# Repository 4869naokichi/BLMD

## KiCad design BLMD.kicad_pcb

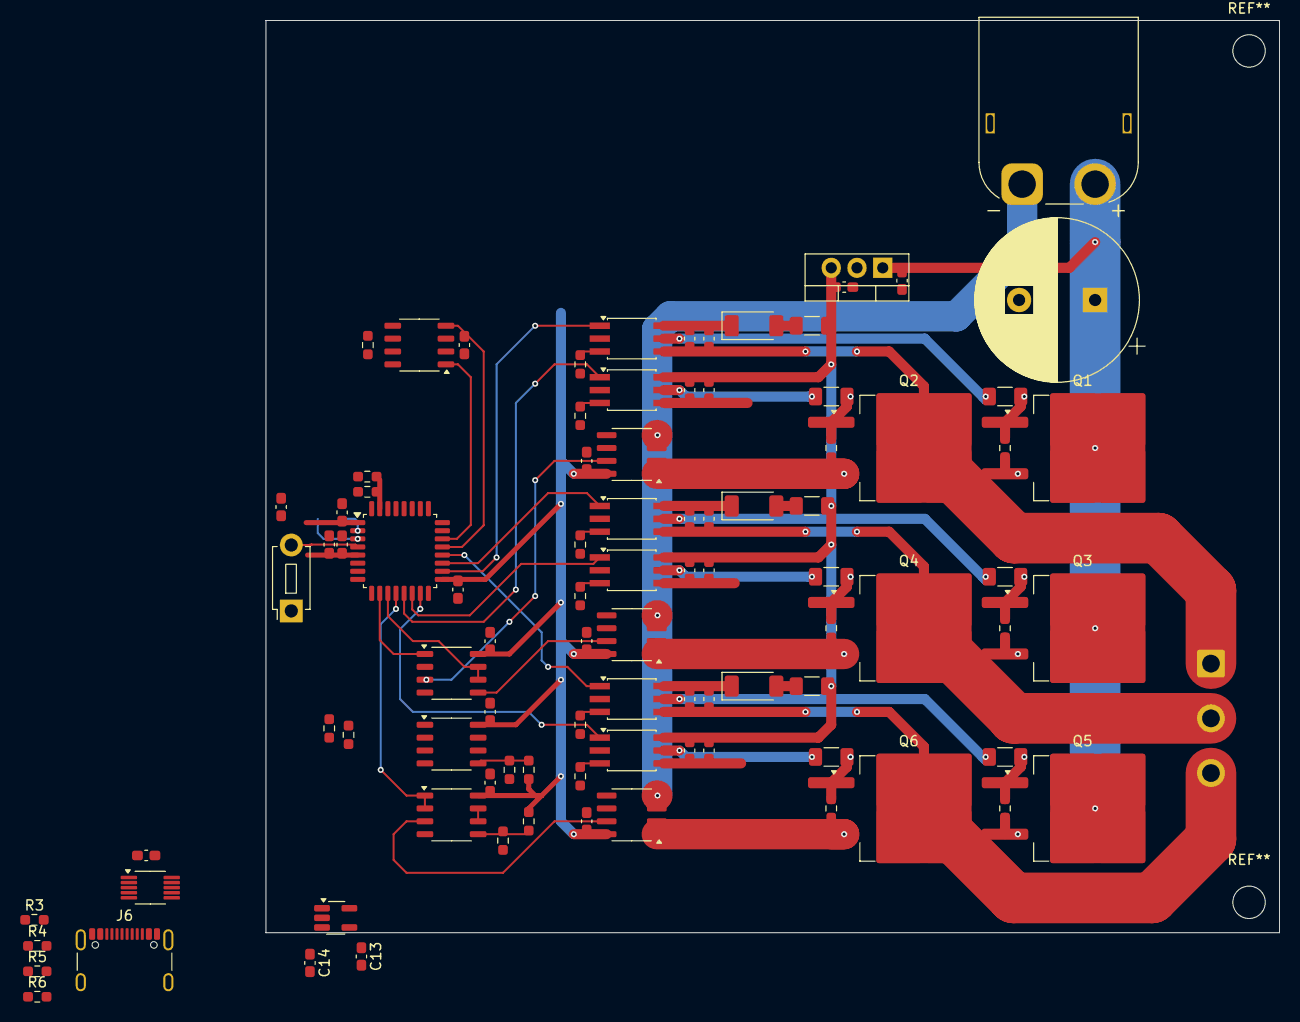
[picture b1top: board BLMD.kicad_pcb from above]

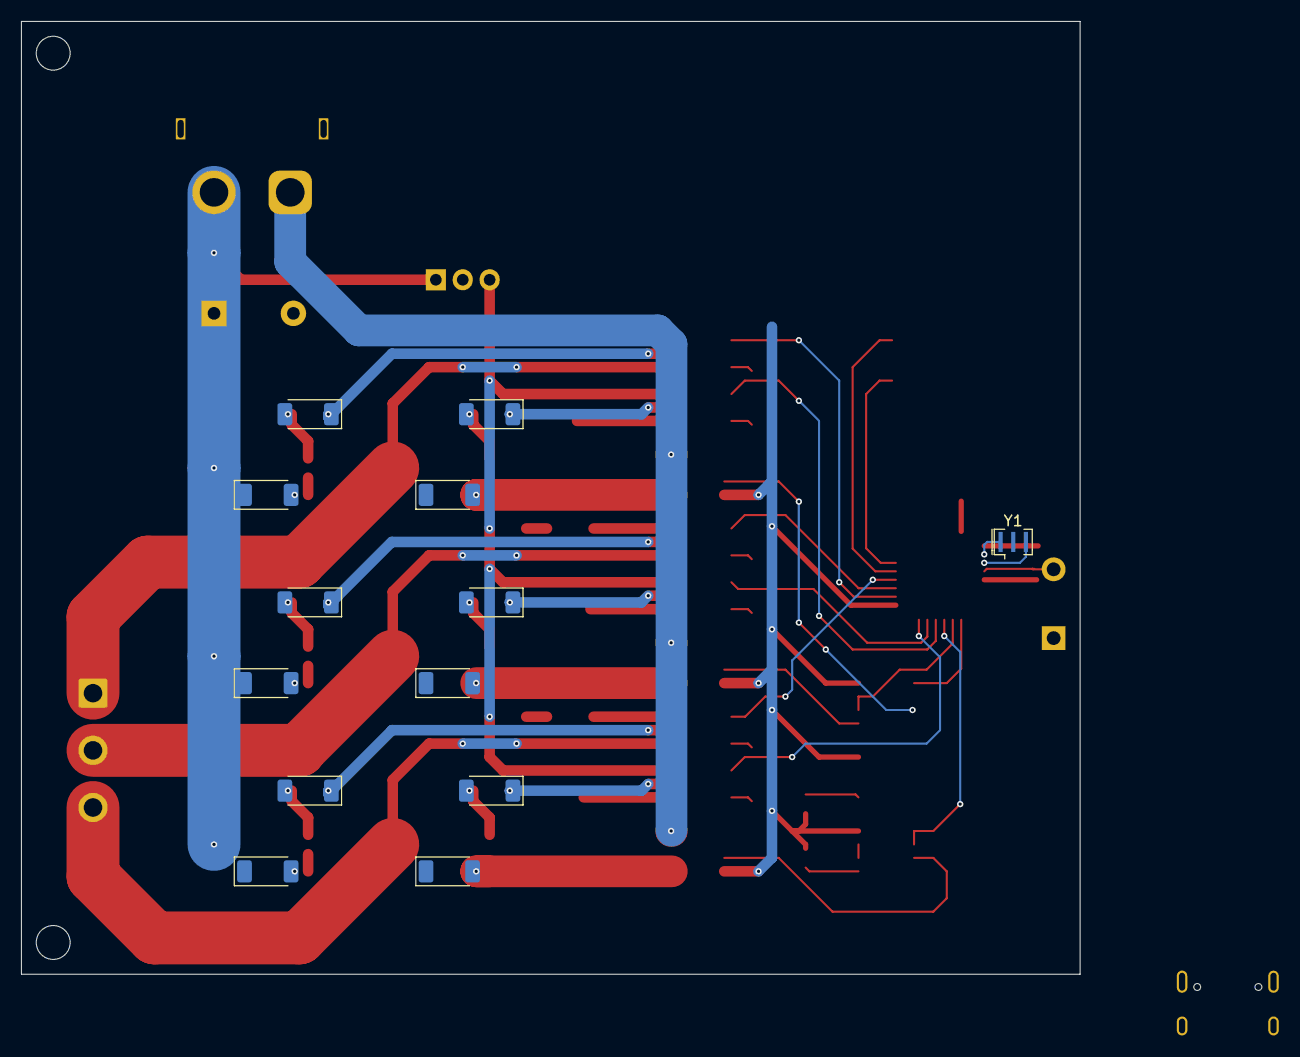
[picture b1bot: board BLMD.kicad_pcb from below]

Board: 2 copper layers, 100.0 x 90.0 mm, 107 parts (13 on the bottom side), 68 nets.

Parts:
C1, C2, C3, C5, C7, C10, C11, C13, C14, C15, C16, C17, C18, C19, C21, C23, C31, C41, C43, C51, C61, C63: 0.1u; C_0603_1608Metric_Pad1.08x0.95mm_HandSolder
C4, C12, C32, C52: 1u; C_0603_1608Metric_Pad1.08x0.95mm_HandSolder
C8: 1000u; CP_Radial_D16.0mm_P7.50mm
C22, C42, C62: 10u; C_0603_1608Metric_Pad1.08x0.95mm_HandSolder
D11, D12, D13, D21, D22, D31, D32, D33, D41, D42, D51, D52, D53, D61, D62: RBR5LAM60A; D_SOD-128
J6: USB_C_Receptacle_USB2.0_14P; USB_C_Receptacle_GCT_USB4105-xx-A_16P_TopMnt_Horizontal
J8: 24V IN; AMASS_XT60PW-M_1x02_P7.20mm_Horizontal
J9: MOTOR; SolderWire-1sqmm_1x03_P5.4mm_D1.4mm_OD2.7mm
Q1, Q2, Q3, Q4, Q5, Q6: RJ1G12BGN; TO-263-2
R1, R17, R18, R19, R20: 10k (DNP); R_0603_1608Metric_Pad0.98x0.95mm_HandSolder
R2, R3, R4, R5, R6, R12, R15, R16, R22, R32, R42, R52, R62: 10k; R_0603_1608Metric_Pad0.98x0.95mm_HandSolder
R7, R14, R24, R34, R44, R54, R64: 120; R_0603_1608Metric_Pad0.98x0.95mm_HandSolder
R11, R21, R31, R41, R51, R61: 4.7; R_1206_3216Metric_Pad1.30x1.75mm_HandSolder
R13, R33, R53: 1.3; R_1206_3216Metric_Pad1.30x1.75mm_HandSolder
SW1: NRST; SW_PUSH_1P1T_6x3.5mm_H4.3_APEM_MJTP1243
U1, U2, U3, U4, U5, U6: TLP152; SO-6_4.4x3.6mm_P1.27mm
U7, U8, U9: ACS711xLCTR-12AB; SOIC-8_3.9x4.9mm_P1.27mm
U10: CH340E; MSOP-10_3x3mm_P0.5mm
U11: STM32F303K8Tx; LQFP-32_7x7mm_P0.8mm
U12: BD41044FJ-C; SOP-8_3.9x4.9mm_P1.27mm
U13: NJM12877; SOT-23-5_HandSoldering
U15: L7812; TO-220-3_Vertical
U16, U17, U18: NJU77552G; SOP-8_3.9x4.9mm_P1.27mm
Y1: 16MHz; Resonator_SMD_Murata_CSTxExxV-3Pin_3.0x1.1mm

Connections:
+3V3: C2.2, C3.2, C4.1, C5.1, C10.2, C14.2, C17.1, C18.1, C19.1, C23.2, C43.2, C63.2, R1.1, R15.1, R17.1, R19.1, U7.8 (VCC), U8.8 (VCC), U9.8 (VCC), U10.7 (VCC), U10.10 (V3), U11.1 (VDD), U11.5 (VDDA), U11.17 (VDD), U13.5 (VO), U16.8 (V+), U17.8 (V+), U18.8 (V+)
+5V: C7.2, C13.2, J6.A4 (VBUS), J6.A9 (VBUS), J6.B4 (VBUS), J6.B9 (VBUS), U12.3 (VCC), U13.1 (VI), U13.3 (CTRL)
+12V: C16.1, C21.1, C22.1, C41.1, C42.1, C61.1, C62.1, R13.1, R33.1, R53.1, U2.6, U4.6, U6.6, U15.3 (OUT)
+24V: C8.1, C15.1, D12.1 (K), D32.1 (K), D52.1 (K), J8.2, Q1.2 (D), Q3.2 (D), Q5.2 (D), U15.1 (IN)
/Inverter/IU: U7.7 (VIOUT), U16.3 (+)
/Inverter/IV: U8.7 (VIOUT), U16.5 (+)
/Inverter/IW: U9.7 (VIOUT), U17.3 (+)
/Inverter/PWMUH: U1.1, U11.18 (PA8)
/Inverter/PWMUL: U2.1, U11.13 (PA7)
/Inverter/PWMVH: U3.1, U11.19 (PA9)
/Inverter/PWMVL: U4.1, U11.14 (PB0)
/Inverter/PWMWH: U5.1, U11.20 (PA10)
/Inverter/PWMWL: U6.1, U11.15 (PB1)
/Inverter/U: C11.2, C12.2, D12.2 (A), D22.1 (K), J9.1, Q1.3 (S), Q2.2 (D), R12.2, U1.4
/Inverter/V: C31.2, C32.2, D32.2 (A), D42.1 (K), J9.2, Q3.3 (S), Q4.2 (D), R32.2, U3.4
/Inverter/W: C51.2, C52.2, D52.2 (A), D62.1 (K), J9.3, Q5.3 (S), Q6.2 (D), R52.2, U5.4
/MCU/ADC1_IN1: U11.6 (PA0), U18.1, U18.2 (-)
/MCU/ADC1_IN2: U11.7 (PA1), U18.6 (-), U18.7
/MCU/CAN_RX: U11.21 (PA11), U12.4 (RXD)
/MCU/CAN_TX: U11.22 (PA12), U12.1 (TXD)
/MCU/IU: U11.10 (PA4), U16.1, U16.2 (-)
/MCU/IV: U11.11 (PA5), U16.6 (-), U16.7
/MCU/IW: U11.12 (PA6), U17.1, U17.2 (-)
/MCU/NRST: C1.1, SW1.2, U11.4 (NRST)
/MCU/USART2_RX: U10.8 (TXD), U11.9 (PA3)
/MCU/USART2_TX: U10.9 (RXD), U11.8 (PA2)
GND: C1.2, C2.1, C3.1, C4.2, C5.2, C7.1, C10.1, C13.1, C14.1, C17.2, C18.2, C19.2, C23.1, C43.1, C63.1, J6.A1 (GND), J6.A12 (GND), J6.B1 (GND), J6.B12 (GND), R2.2, R3.2, R4.2, R5.2, R6.2, R14.1, R16.2, R18.2, R20.2, R24.1, R34.1, R44.1, R54.1, R64.1, SW1.1, U7.5 (GND), U8.5 (GND), U9.5 (GND), U10.3 (GND), U11.16 (VSS), U11.32 (VSS), U12.2 (GND), U12.8 (STB), U13.2 (GND), U16.4 (V-), U17.4 (V-), U18.4 (V-), Y1.2
GNDPWR: C8.2, C15.2, C16.2, J8.1, U7.3 (IP-), U7.4 (IP-), U8.3 (IP-), U8.4 (IP-), U9.3 (IP-), U9.4 (IP-), U15.2 (GND)
unnamed: D11.2 (A), Q1.1 (G), R11.2, R12.1
unnamed: D11.1 (K), R11.1, U1.5
unnamed: D13.2 (A), R13.2
unnamed: C11.1, C12.1, D13.1 (K), U1.6
unnamed: D21.2 (A), Q2.1 (G), R21.2, R22.1
unnamed: D21.1 (K), R21.1, U2.5
unnamed: C21.2, C22.2, D22.2 (A), Q2.3 (S), R22.2, U2.4, U7.1 (IP+), U7.2 (IP+)
unnamed: D31.2 (A), Q3.1 (G), R31.2, R32.1
unnamed: D31.1 (K), R31.1, U3.5
unnamed: D33.2 (A), R33.2
unnamed: C31.1, C32.1, D33.1 (K), U3.6
unnamed: D41.2 (A), Q4.1 (G), R41.2, R42.1
unnamed: D41.1 (K), R41.1, U4.5
unnamed: C41.2, C42.2, D42.2 (A), Q4.3 (S), R42.2, U4.4, U8.1 (IP+), U8.2 (IP+)
unnamed: D51.2 (A), Q5.1 (G), R51.2, R52.1
unnamed: D51.1 (K), R51.1, U5.5
unnamed: D53.2 (A), R53.2
unnamed: C51.1, C52.1, D53.1 (K), U5.6
unnamed: D61.2 (A), Q6.1 (G), R61.2, R62.1
unnamed: D61.1 (K), R61.1, U6.5
unnamed: C61.2, C62.2, D62.2 (A), Q6.3 (S), R62.2, U6.4, U9.1 (IP+), U9.2 (IP+)
unnamed: R7.2, U12.6 (CANL)
unnamed: R7.1, U12.7 (CANH)
unnamed: R19.2, R20.1, U18.5 (+)
unnamed: R17.2, R18.1, U18.3 (+)
unnamed: J6.A5 (CC1), R3.1, R4.1
unnamed: J6.B5 (CC2), R5.1, R6.1
unnamed: R14.2, U1.3
unnamed: R24.2, U2.3
unnamed: R34.2, U3.3
unnamed: R44.2, U4.3
unnamed: R54.2, U5.3
unnamed: R64.2, U6.3
unnamed: J6.A6 (D+), J6.B6 (D+), U10.1 (UD+)
unnamed: J6.A7 (D-), J6.B7 (D-), U10.2 (UD-)
unnamed: R1.2, R2.1, U11.31 (BOOT0)
unnamed: U11.2 (PF0), Y1.1
unnamed: U11.3 (PF1), Y1.3
unnamed: R15.2, R16.1, U17.5 (+)
unnamed: U17.6 (-), U17.7

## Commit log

2024-06-21 chore: Add KiCad project files for BLMD
2024-06-29 chore: Exclude power pin not driven errors in ERC
2024-07-03 feat: Add symbols for BD41044FJ-C and NJM12877
    The commit adds symbols for the BD41044FJ-C and NJM12877 components to the KiCad project.
2024-07-03 chore: Update KiCad project files for BLMD
2024-07-06 feat: Add symbols for BD41044FJ-C and NJM12877
